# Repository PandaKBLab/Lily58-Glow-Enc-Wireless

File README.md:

# Lily58 × qtkb Glow + Rotary Encoders designed for Wireless

Lily58 is 6×4+4keys column-staggered split keyboard.

This is a project to edit the Lily58 x qtkb Glow + Rotary Encoders to make it easily compatible with wireless settings. This is designed for the nice!nano, and will have a battery disconnect switch, no TRRS jack, and underglow LEDs (a later task is to add per-key LEDs). Very much a work in progress until there is an initial release. Hoping to have this modified and ready shortly after I receive my Boardsource.xyz Lulu (Lily58 compatible) case. Stay tuned!

Firmware repo: https://github.com/iasoren/Lily58-Glow-Enc-Wireless-ZMK

| Task      | Status     | Issues        | ETA         |
|-----------|------------|---------------|-------------|
| Schematic | Pending | Need to fix underglow | Unknown |
| PCB layouts | Pending | Trying to revert to dual-sided design | Unknown |
| Underglow | Pending | See above | Unknown |
| Backlight | Planning | Planning | Undetermined |

Bill of Materials:
* 2x PCB
* 4x OS102011MA1QN1 Slide Switch
* 2x nice!nano
* 1x EC11 encoder (or 2x, personal preference)
* 56x Hotswap sockets
* 60x SK6812 mini-E LEDs
* 20x WS2812b LEDs
* 58x 1N4148W Thru-hole Diodes (or SMD diodes)

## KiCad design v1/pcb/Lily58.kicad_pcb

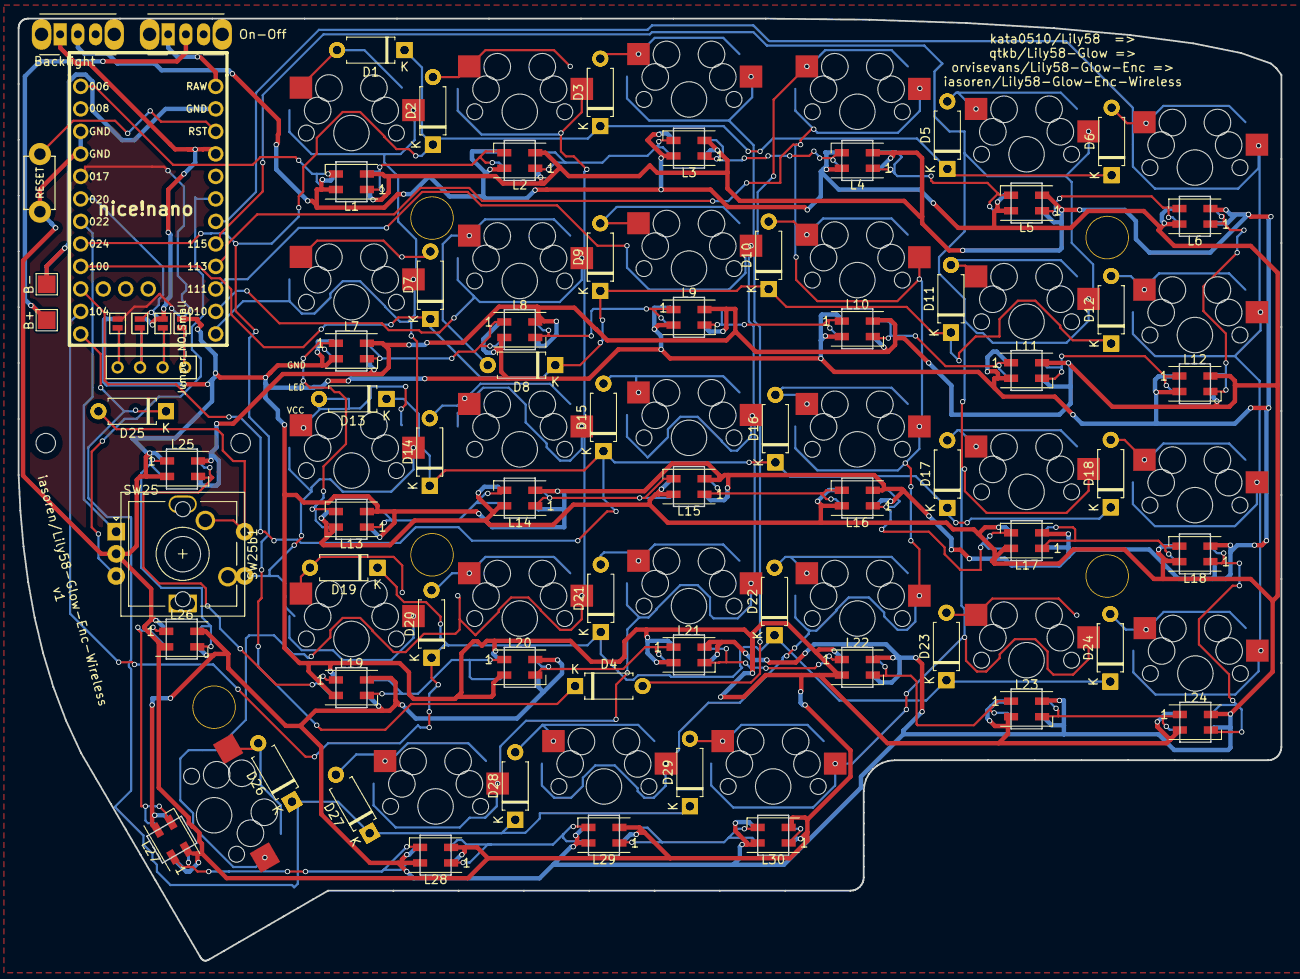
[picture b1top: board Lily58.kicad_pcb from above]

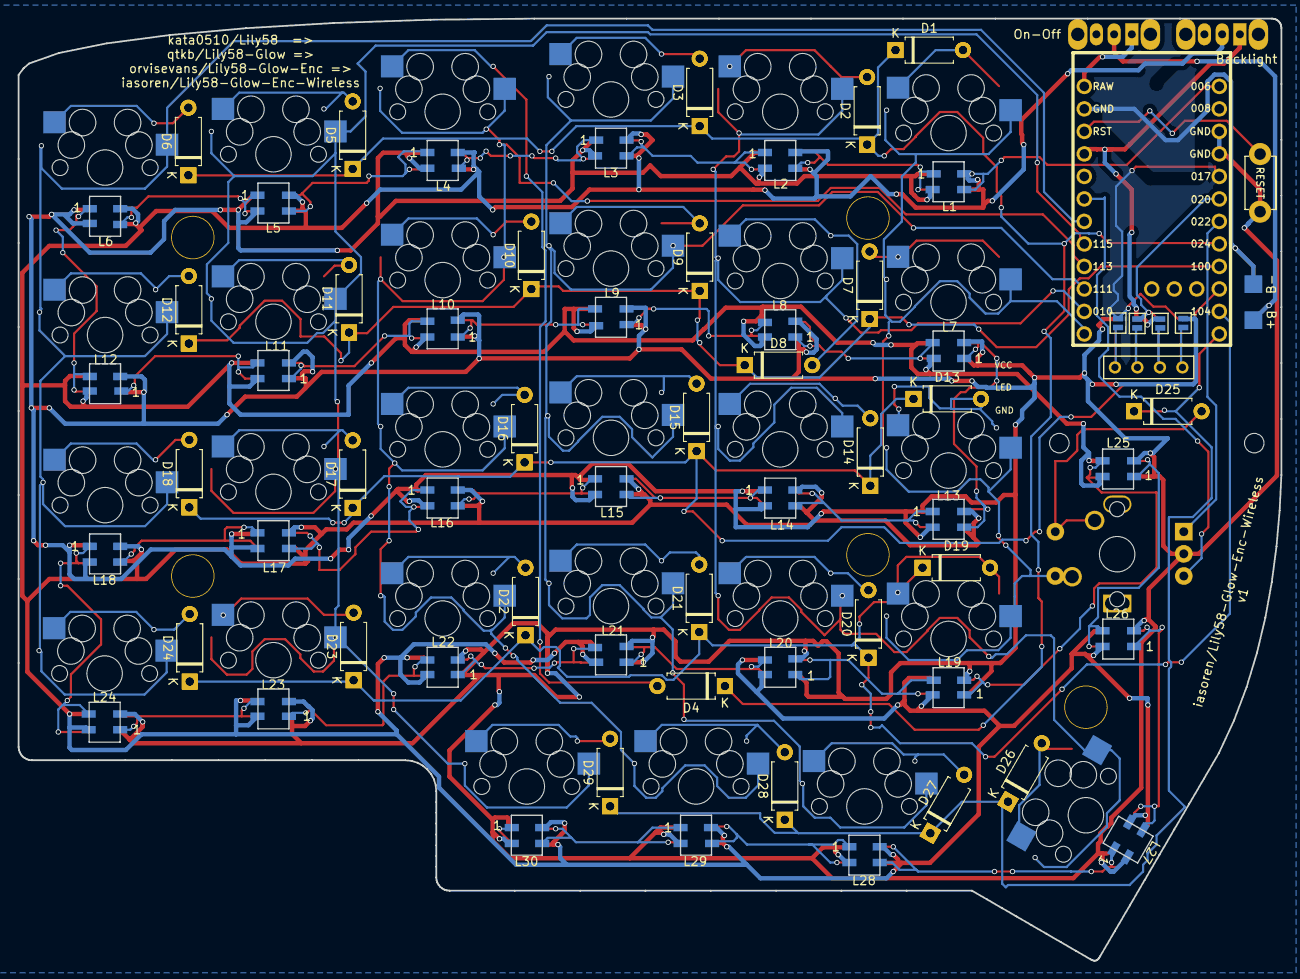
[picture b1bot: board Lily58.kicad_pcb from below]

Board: 2 copper layers, 142.5 x 106.3 mm, 140 parts (33 on the bottom side), 84 nets.

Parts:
B+: Conn_01x01_Male; TestPoint_Pad_2.0x2.0mm
B-: Conn_01x01_Male; TestPoint_Pad_2.0x2.0mm
Backlight: SW_DIP_x01; SW_CuK_OS102011MA1QN1_SPDT_Angled
D1, D1#2, D2, D2#2, D3, D3#2, D4, D4#2, D5, D5#2, D6, D6#2, D7, D7#2, D8, D8#2, D9, D9#2, D10, D10#2, D11, D11#2, D12, D12#2, D13, D13#2, D14, D14#2, D15, D15#2, D16, D16#2, D17, D17#2, D18, D18#2, D19, D19#2, D20, D20#2, D21, D21#2, D22, D22#2, D23, D23#2, D24, D24#2, D25, D25#2, D26, D26#2, D27, D27#2, D28, D28#2, D29, D29#2: D; D_A-405_P7.62mm_Horizontal
JP1, JP2, JP3, JP4, JP5, JP6, JP7, JP8: Jumper_NO_Small; Jumper
L1, L2, L3, L4, L5, L6, L7, L8, L9, L10, L11, L12, L13, L14, L15, L16, L17, L18, L19, L20, L21, L22, L23, L24, L25, L26, L27, L28, L29, L30: SK6812mini; LED_SK6812MINI_PLCC4_3.5x3.5mm_P1.75mm
On-Off: SW_DIP_x01; SW_CuK_OS102011MA1QN1_SPDT_Angled
P4: OLED; MY_SIL-4
RSW1: SW_RST; TACT_SWITCH_TVBP06
SW1, SW2, SW3, SW4, SW5, SW6, SW7, SW8, SW9, SW10, SW11, SW12, SW13, SW14, SW15, SW16, SW17, SW18, SW19, SW20, SW21, SW22, SW23, SW24, SW26, SW27, SW28, SW29: SW_PUSH; MX_Socket_18mm
SW25: Rotary_Encoder_Switch; RotaryEncoder_Alps_EC11E-Switch_Vertical_H20mm
SW25b1: SW_Cherry_MX_1.00u_PCB
TH1, TH2: HOLE; HOLE_M2
TH3, TH4, TH5, TH6, TH7: HOLE; HOLE_M2_TH
U1: NiceNano; nice_nano

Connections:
Batt+: On-Off.1, U1.24 (RAW)
Batt-: B-.1, U1.23 (GND)
GND: JP1.2, JP8.2, L1.2 (VSS), L2.2 (VSS), L3.2 (VSS), L4.2 (VSS), L5.2 (VSS), L6.2 (VSS), L7.2 (VSS), L8.2 (VSS), L9.2 (VSS), L10.2 (VSS), L11.2 (VSS), L12.2 (VSS), L13.2 (VSS), L14.2 (VSS), L15.2 (VSS), L16.2 (VSS), L17.2 (VSS), L18.2 (VSS), L19.2 (VSS), L20.2 (VSS), L21.2 (VSS), L22.2 (VSS), L23.2 (VSS), L24.2 (VSS), L25.2 (VSS), L26.2 (VSS), L27.2 (VSS), L28.2 (VSS), L29.2 (VSS), L30.2 (VSS), RSW1.1, SW25.C, U1.3 (GND), U1.4 (GND)
unnamed: D1.2 (A), D1#2.2 (A), SW1.2
unnamed: D2.2 (A), D2#2.2 (A), SW2.2
unnamed: D3.2 (A), D3#2.2 (A), SW3.2
unnamed: D4.2 (A), D4#2.2 (A), SW4.2
unnamed: D5.2 (A), D5#2.2 (A), SW5.2
unnamed: D6.2 (A), D6#2.2 (A), SW6.2
unnamed: D7.2 (A), D7#2.2 (A), SW7.2
unnamed: D8.2 (A), D8#2.2 (A), SW8.2
unnamed: D9.2 (A), D9#2.2 (A), SW9.2
unnamed: D10.2 (A), D10#2.2 (A), SW10.2
unnamed: D11.2 (A), D11#2.2 (A), SW11.2
unnamed: D12.2 (A), D12#2.2 (A), SW12.2
unnamed: D13.2 (A), D13#2.2 (A), SW13.2
unnamed: D14.2 (A), D14#2.2 (A), SW14.2
unnamed: D15.2 (A), D15#2.2 (A), SW15.2
unnamed: D16.2 (A), D16#2.2 (A), SW16.2
unnamed: D17.2 (A), D17#2.2 (A), SW17.2
unnamed: D18.2 (A), D18#2.2 (A), SW18.2
unnamed: D19.2 (A), D19#2.2 (A), SW19.2
unnamed: D20.2 (A), D20#2.2 (A), SW20.2
unnamed: D21.2 (A), D21#2.2 (A), SW21.2
unnamed: D22.2 (A), D22#2.2 (A), SW22.2
unnamed: D23.2 (A), D23#2.2 (A), SW23.2
unnamed: D24.2 (A), D24#2.2 (A), SW24.2
unnamed: D25.2 (A), D25#2.2 (A), SW25.S2, SW25b1.2
unnamed: D26.2 (A), D26#2.2 (A), SW26.2
unnamed: D27.2 (A), D27#2.2 (A), SW27.2
unnamed: D28.2 (A), D28#2.2 (A), SW28.2
unnamed: D29.2 (A), D29#2.2 (A), SW29.2
unnamed: B+.1, On-Off.2
unnamed: JP1.1, JP5.1, P4.4
unnamed: JP2.1, JP6.1, P4.3
unnamed: JP3.1, JP7.1, P4.2
unnamed: JP4.1, JP8.1, P4.1
unnamed: L1.1 (DOUT), L2.3 (DIN)
unnamed: Backlight.2, L1.3 (DIN), L1.4 (VDD), L2.4 (VDD), L3.4 (VDD), L4.4 (VDD), L5.4 (VDD), L6.4 (VDD), L7.4 (VDD), L8.4 (VDD), L9.4 (VDD), L10.4 (VDD), L11.4 (VDD), L12.4 (VDD), L13.4 (VDD), L14.4 (VDD), L15.4 (VDD), L16.4 (VDD), L17.4 (VDD), L18.4 (VDD), L19.4 (VDD), L20.4 (VDD), L21.4 (VDD), L22.4 (VDD), L23.4 (VDD), L24.4 (VDD), L25.4 (VDD), L26.4 (VDD), L27.4 (VDD), L28.4 (VDD), L29.4 (VDD), L30.4 (VDD), U1.1 (TX(PD3))
unnamed: L2.1 (DOUT), L3.3 (DIN)
unnamed: L3.1 (DOUT), L4.3 (DIN)
unnamed: L4.1 (DOUT), L5.3 (DIN)
unnamed: L5.1 (DOUT), L6.3 (DIN)
unnamed: L7.3 (DIN), L8.1 (DOUT)
unnamed: L8.3 (DIN), L9.1 (DOUT)
unnamed: L9.3 (DIN), L10.1 (DOUT)
unnamed: L10.3 (DIN), L11.1 (DOUT)
unnamed: L11.3 (DIN), L12.1 (DOUT)
unnamed: L6.1 (DOUT), L12.3 (DIN)
unnamed: L13.1 (DOUT), L14.3 (DIN)
unnamed: L7.1 (DOUT), L13.3 (DIN)
unnamed: L14.1 (DOUT), L15.3 (DIN)
unnamed: L15.1 (DOUT), L16.3 (DIN)
unnamed: L16.1 (DOUT), L17.3 (DIN)
unnamed: L17.1 (DOUT), L18.3 (DIN)
unnamed: L18.1 (DOUT), L24.3 (DIN)
unnamed: L19.1 (DOUT), L25.3 (DIN)
unnamed: L19.3 (DIN), L20.1 (DOUT)
unnamed: L20.3 (DIN), L21.1 (DOUT)
unnamed: L21.3 (DIN), L22.1 (DOUT)
unnamed: L22.3 (DIN), L23.1 (DOUT)
unnamed: L23.3 (DIN), L24.1 (DOUT)
unnamed: L25.1 (DOUT), L26.3 (DIN)
unnamed: L26.1 (DOUT), L27.3 (DIN)
unnamed: L27.1 (DOUT), L28.3 (DIN)
unnamed: L28.1 (DOUT), L29.3 (DIN)
unnamed: L29.1 (DOUT), L30.3 (DIN)
RESET: RSW1.2, U1.22 (RST)
SCL: JP3.2, JP6.2, U1.6 (SCL(PD0))
SDA: JP4.2, JP5.2, U1.5 (SDA(PD1))
VCC: Backlight.1, JP2.2, JP7.2, U1.21 (VCC)
col0: SW6.1, SW12.1, SW18.1, SW24.1, U1.18 (A1(PF6))
col1: SW5.1, SW11.1, SW17.1, SW23.1, SW29.1, U1.17 (A0(PF7))
col2: SW4.1, SW10.1, SW16.1, SW22.1, SW28.1, U1.16 (D15(PB1))
col3: SW3.1, SW9.1, SW15.1, SW21.1, SW27.1, U1.15 (D14(PB3))
col4: SW2.1, SW8.1, SW14.1, SW20.1, SW26.1, U1.14 (D16(PB2))
col5: SW1.1, SW7.1, SW13.1, SW19.1, SW25.S1, SW25b1.1, U1.13 (D10(PB6))
enc1: SW25.A, U1.7 (D4(PD4))
enc2: SW25.B, U1.19 (A2(PF5))
row0: D1.1 (K), D1#2.1 (K), D2.1 (K), D2#2.1 (K), D3.1 (K), D3#2.1 (K), D4.1 (K), D4#2.1 (K), D5.1 (K), D5#2.1 (K), D6.1 (K), D6#2.1 (K), U1.8 (D5(PC6))
row1: D7.1 (K), D7#2.1 (K), D8.1 (K), D8#2.1 (K), D9.1 (K), D9#2.1 (K), D10.1 (K), D10#2.1 (K), D11.1 (K), D11#2.1 (K), D12.1 (K), D12#2.1 (K), U1.9 (D6(PD7))
row2: D13.1 (K), D13#2.1 (K), D14.1 (K), D14#2.1 (K), D15.1 (K), D15#2.1 (K), D16.1 (K), D16#2.1 (K), D17.1 (K), D17#2.1 (K), D18.1 (K), D18#2.1 (K), U1.10 (D7(PE6))
row3: D19.1 (K), D19#2.1 (K), D20.1 (K), D20#2.1 (K), D21.1 (K), D21#2.1 (K), D22.1 (K), D22#2.1 (K), D23.1 (K), D23#2.1 (K), D24.1 (K), D24#2.1 (K), U1.11 (D8(PB4))
row4: D25.1 (K), D25#2.1 (K), D26.1 (K), D26#2.1 (K), D27.1 (K), D27#2.1 (K), D28.1 (K), D28#2.1 (K), D29.1 (K), D29#2.1 (K), U1.12 (D9(PB5))

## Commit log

2022-02-17 Update README.md
    Updated the readme
2022-02-17 File Update
    Files update
2022-02-18 Basic PCB updates
    Updated some silkscreen, have to learn how to use this program better
2022-02-20 Update file layout
2022-02-22 Updates to schematics
    Might just scrap all of the traces and start from scratch...
2022-02-23 Starting PCB from scratch, and making single sided boards
2022-03-23 Reverted to base model to try again
2022-03-28 Working on Vias
2022-04-01 Add libraries, new design
    Turns out DIP switches aren't rated for the LED current, so I need a SPDT switch with a diode placed in between. This means you can have the backlight on, none on, or the backlight and underglow on. 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
2022-04-04 Some file structure changes + lib files
2022-04-04 Update libraries
2022-04-04 add new libraries
2022-04-07 Some more wiring updates
2022-04-14 Updates to files and layout
2022-05-03 Progress update
    Started on BOM, progress update
2022-05-04 File Cleanup
    Worked a bit more on LEDs, started initial firmware settings. Ordered some nice!nanos and soon to have prototype boards in to work with
2022-05-04 Added firmware
2022-05-04 Firmware
2022-05-04 file update
2022-05-04 Add firmware files
2022-05-04 update name
2022-05-04 remove files
2022-05-04 Added files back
2022-05-04 Firmware start
2022-05-04 Update lily58.conf
    Enable OLED and EC11
2022-05-04 Update build.yaml
    Add nice!nano v1 build options
2022-05-05 Backlight LEDs
    Finished the routing for backlight LEDs, adjusted nice!nano placement and power placement. Moved some text around to empty board spots, made sure that silkscreen was duplicated to both sides. Uploade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
2022-05-05 removed extra files
2022-05-05 Moving firmware to separate repo
    Lily58-Glow-Enc-Wireless-ZMK
2022-05-05 Update README.md
    Added link to firmware side
2022-05-06 Update build.yml
    Remove workflow
2022-05-27 Replacing V1
    Starting from scratch for V1 due to some issues
2022-05-27 Remove PCB
2022-05-27 Add V2 folder
2022-05-31 Fixes to V1
    Fixing V1 errors, v2 is working
2022-06-01 Hopefully Fixed PCB
    Added in the option to replace the right hand encoder with a switch, must be soldered though. Hopefully this PCB will work this time around!
2022-06-02 Keymap updates
2022-06-14 Folder Layout Updates
2022-06-15 Some edits
    Added in underglow LEDs to the schematics, started moving around the PCB items.
    Deciding between TH and SMD diodes (or both)
2022-06-20 More PCB edits
2022-09-28 Split keyboard PCB, remove LEDs
    Split the keyboard PCBs so it is no longer double sided, removed per-key lighting for this iteration due to ZMK support. Thinking about RP2040+wireless for a future iteration to add per-key lighting 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
2022-09-29 Battery moving
    Moving battery solder points
